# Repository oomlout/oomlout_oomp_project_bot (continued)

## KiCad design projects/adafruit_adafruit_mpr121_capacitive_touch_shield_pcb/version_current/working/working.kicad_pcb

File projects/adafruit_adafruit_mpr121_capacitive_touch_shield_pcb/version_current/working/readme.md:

# OOMP Project  
## Adafruit-MPR121-Capacitive-Touch-Shield-PCB  by adafruit  
  
oomp key: oomp_projects_flat_adafruit_adafruit_mpr121_capacitive_touch_shield_pcb  
(snippet of original readme)  
  
-- Adafruit MPR121 Capacitive Touch Shield PCB  
<a href="http://www.adafruit.com/products/2024"><br/>  
Click here to purchase one from the Adafruit shop</a>  
  
This touch-able add on shield for Arduinos will inspire your next interactive project with 12 capacitive touch sensors. Capacitive touch sensing works by detecting when a person (or animal) has touched one of the sensor electrodes. Capacitive touch sensing used for stuff like touch-reactive tablets and phones, as well as control panels for appliances, which is where you may have used it before. This shield allows you to create electronics that can react to human touch, with up to 12 individual sensors.  
  
The shield has 12 'figure 8' holes in it that can be gripped onto with alligator clip cables. Attach one side of the clip to the shield and the other side to something electrically conductive (like metal) or full of water (like vegetables or fruit!) Then start up our handy Arduino library to detect when the object is touched. That's pretty much it, very easy! For advanced users, you can also solder to a pad to make a slimmer & more permanent connection. Works great with any Arduino as it only uses the I2C pins (SCL & SDA).  
  
It uses the same chip as our MPR121 12-Key Capacitive Touch Sensor Breakout so you can duplicate the library and code! We have examples for reading touches. Using an Arduino Leonardo and a little bit of creativity you can use it to turn touches into keybo  
  full source readme at [readme_src.md](readme_src.md)  
  
source repo at: [https://github.com/adafruit/Adafruit-MPR121-Capacitive-Touch-Shield-PCB](https://github.com/adafruit/Adafruit-MPR121-Capacitive-Touch-Shield-PCB)  
## Board  

## Schematic  

[schematic pdf](working_schematic.pdf)  
## Images

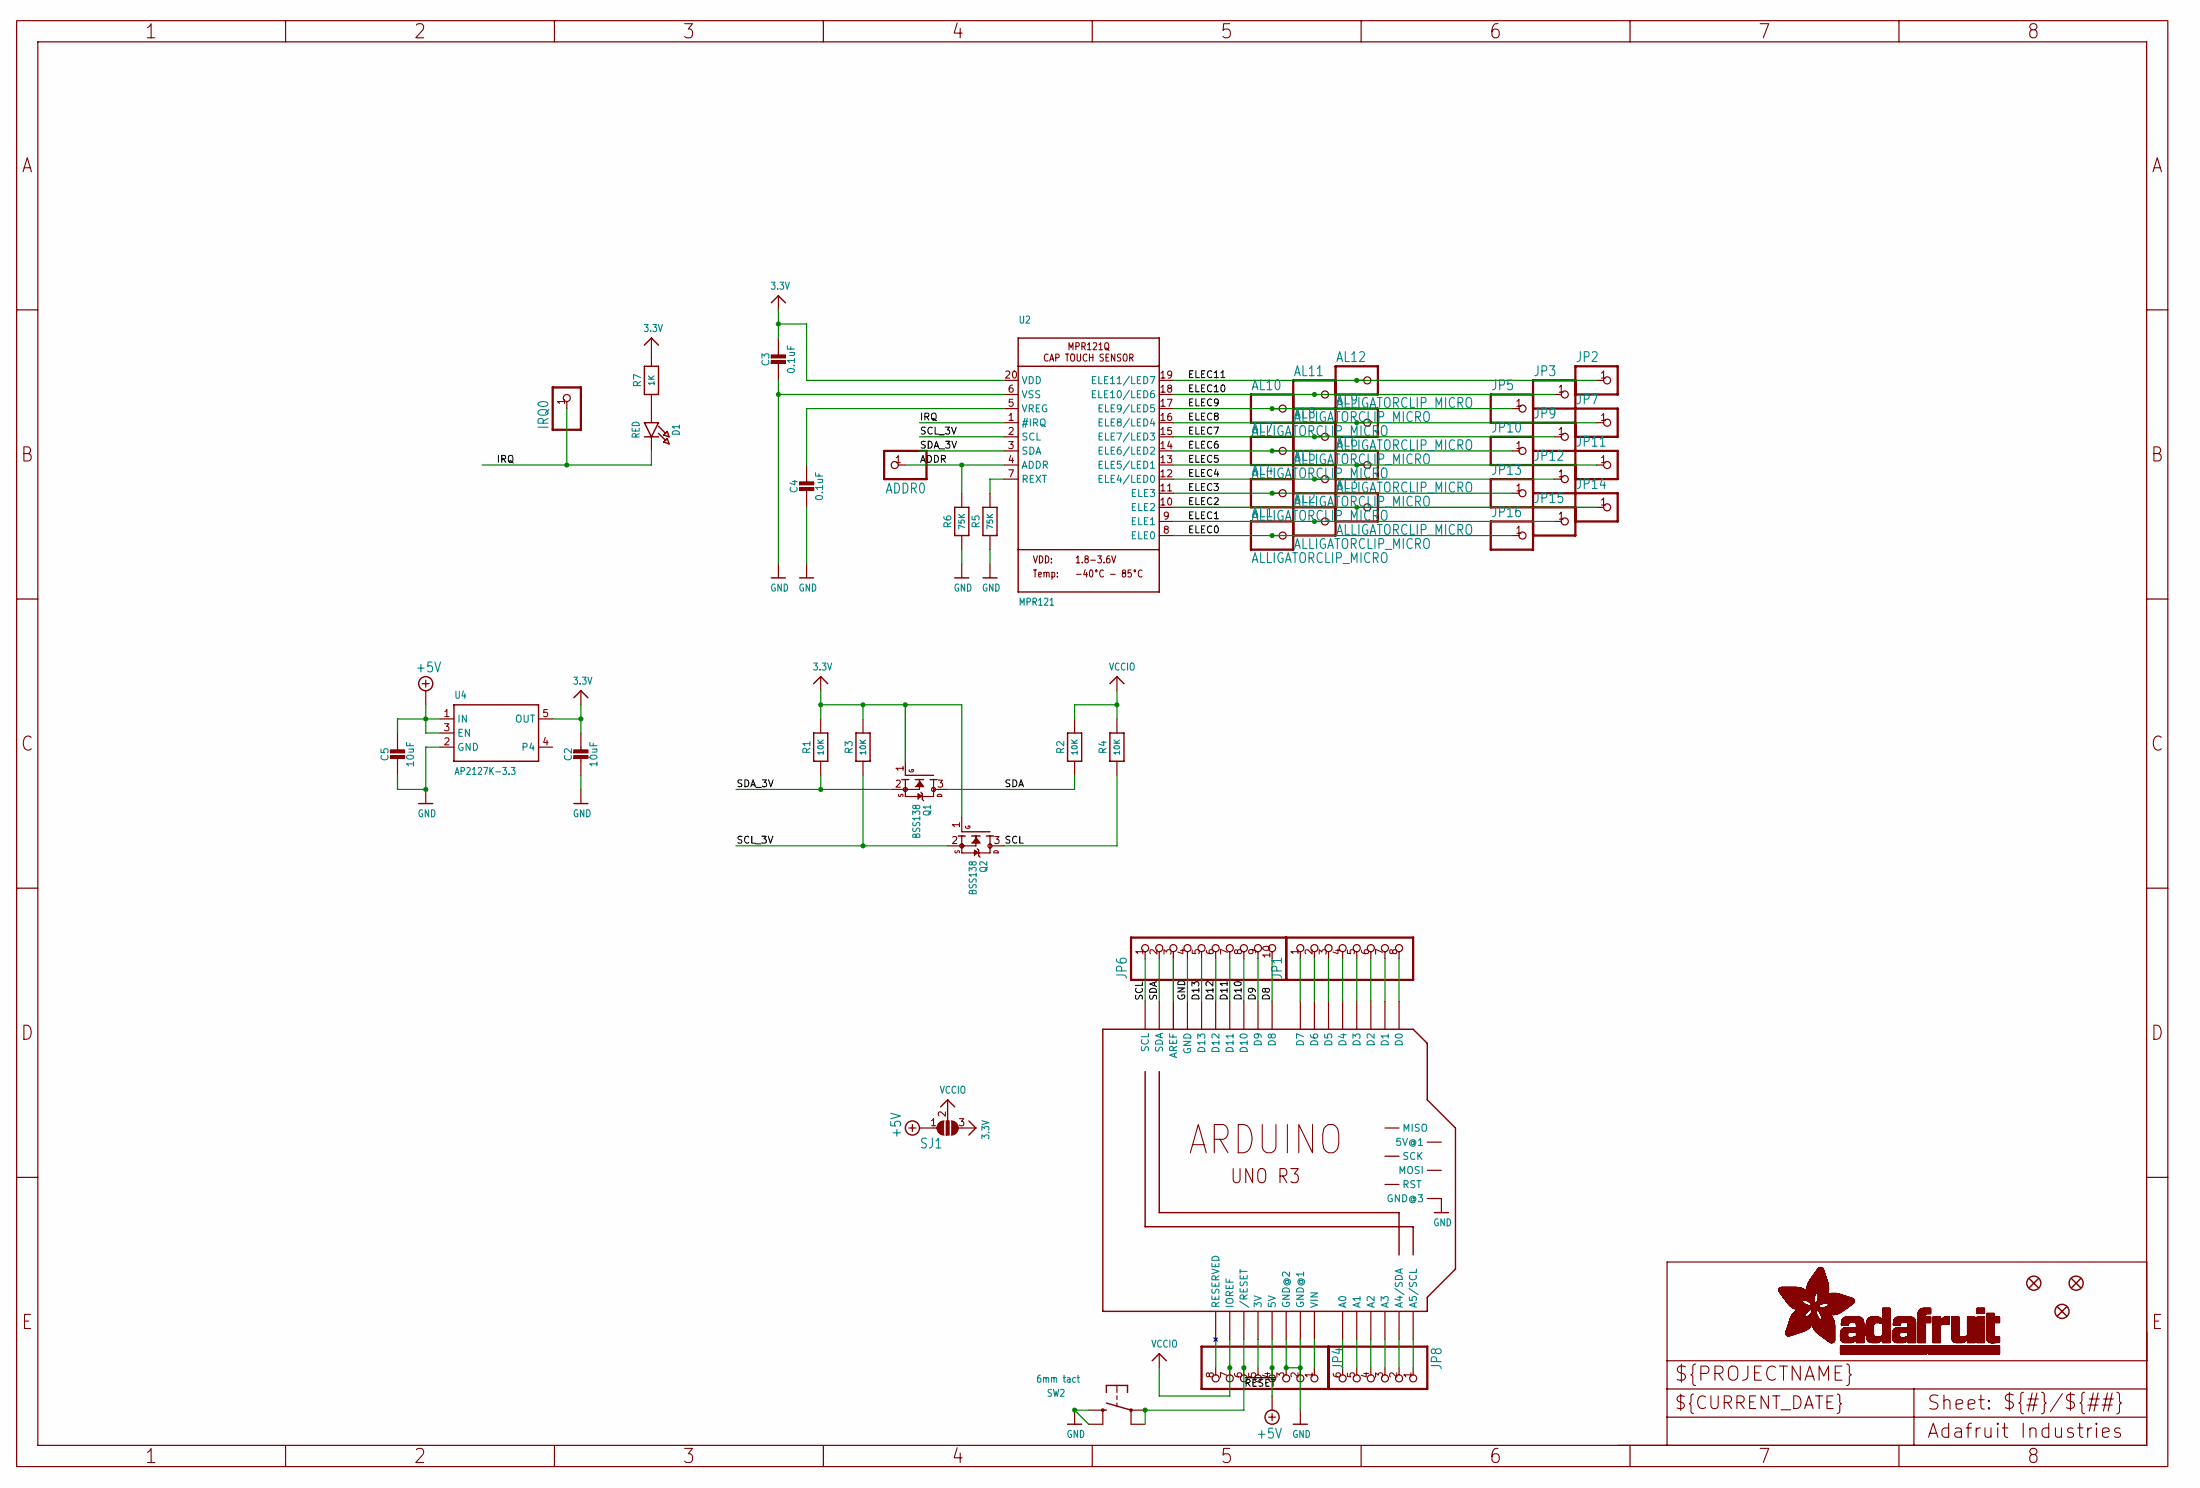
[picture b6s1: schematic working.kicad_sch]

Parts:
ADDR0: HEADER-1X1ROUND; 1X01_ROUND
AL1, AL2, AL3, AL4, AL5, AL6, AL7, AL8, AL9, AL10, AL11, AL12: ALLIGATORCLIP_MICRO; ALLIGATORCLIP
C2, C5: 10uF; 0805-NO
C3, C4: 0.1uF; 0805-NO
D1: RED; CHIPLED_0805_NOOUTLINE
FID1, FID2, FID3: FIDUCIAL_1MM
IRQ0: HEADER-1X1ROUND; 1X01_ROUND
JP1, JP4: PINHD-1X8CLEANBIG; 1X08-CLEANBIG
JP2, JP3, JP5, JP7, JP9, JP10, JP11, JP12, JP13, JP14, JP15, JP16: HEADER-1X1ROUND; 1X01_ROUND
JP6: HEADER-1X1070MIL; 1X10_ROUND70
JP8: PINHD-1X6CB; 1X06-CLEANBIG
Q1, Q2: BSS138; SOT23-WIDE
R1, R2, R3, R4: 10K; 0805-NO
R5, R6: 75K; 0805-NO
R7: 1K; 0805-NO
SJ1: SOLDERJUMPER_2WAY; SOLDERJUMPER_2WAY_OPEN_NOPASTE
SW2: 6mm tact; 6MMX6MM_TACTILE_SMT
U2: MPR121; QFN20_3MM_NOTHERMAL
U4: AP2127K-3.3; SOT23-5
U$41: ARDUINO_R3_ICSP_NODIM; ARDUINOR3_ICSP_NODIM

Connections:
3.3V: C2.1, C3.1, Q1.1 (G), Q2.1 (G), R1.2, R3.2, R7.2, SJ1.3, U2.20 (VDD), U4.5 (OUT)
+3V: JP4.5, U$41.3V
+5V: C5.1, JP4.4, SJ1.1, U4.1 (IN), U4.3 (EN), U$41.5V
A0: JP8.6, U$41.A0
A1: JP8.5, U$41.A1
A2: JP8.4, U$41.A2
A3: JP8.3, U$41.A3
A4: JP8.2, U$41.A4 (A4/SDA)
A5: JP8.1, U$41.A5 (A5/SCL)
ADDR: ADDR0.1, R6.2, U2.4 (ADDR)
AREF: JP6.3, U$41.AREF
D0: JP1.8, U$41.D0
D1: JP1.7, U$41.D1
D2: JP1.6, U$41.D2
D3: JP1.5, U$41.D3
D4: JP1.4, U$41.D4
D5: JP1.3, U$41.D5
D6: JP1.2, U$41.D6
D7: JP1.1, U$41.D7
D8: JP6.10, U$41.D8
D9: JP6.9, U$41.D9
D10: JP6.8, U$41.D10
D11: JP6.7, U$41.D11
D12: JP6.6, U$41.D12
D13: JP6.5, U$41.D13
ELEC0: AL1.P$1, AL1.P$2, JP16.1, U2.8 (ELE0)
ELEC1: AL2.P$1, AL2.P$2, JP15.1, U2.9 (ELE1)
ELEC2: AL3.P$1, AL3.P$2, JP14.1, U2.10 (ELE2)
ELEC3: AL4.P$1, AL4.P$2, JP13.1, U2.11 (ELE3)
ELEC4: AL5.P$1, AL5.P$2, JP12.1, U2.12 (ELE4/LED0)
ELEC5: AL6.P$1, AL6.P$2, JP11.1, U2.13 (ELE5/LED1)
ELEC6: AL7.P$1, AL7.P$2, JP10.1, U2.14 (ELE6/LED2)
ELEC7: AL8.P$1, AL8.P$2, JP9.1, U2.15 (ELE7/LED3)
ELEC8: AL9.P$1, AL9.P$2, JP7.1, U2.16 (ELE8/LED4)
ELEC9: AL10.P$1, AL10.P$2, JP5.1, U2.17 (ELE9/LED5)
ELEC10: AL11.P$1, AL11.P$2, JP3.1, U2.18 (ELE10/LED6)
ELEC11: AL12.P$1, AL12.P$2, JP2.1, U2.19 (ELE11/LED7)
GND: C2.2, C3.2, C4.2, C5.2, JP4.2, JP4.3, JP6.4, R5.1, R6.1, SW2.B (S), SW2.B' (S1), U2.6 (VSS), U4.2 (GND), U$41.GND, U$41.GND@1 (GND@2), U$41.GND@2 (GND@3), U$41.GND@3 (GND@1)
IRQ: D1.C, IRQ0.1, U2.1 (#IRQ)
unnamed: C4.1, U2.5 (VREG)
unnamed: R5.2, U2.7 (REXT)
unnamed: D1.A, R7.1
NC: JP4.8, U$41.RESERVED
SCL: JP6.1, Q2.3 (D), R4.1, U$41.SCL
SCL_3V: Q2.2 (S), R3.1, U2.2 (SCL)
SDA: JP6.2, Q1.3 (D), R2.1, U$41.SDA
SDA_3V: Q1.2 (S), R1.1, U2.3 (SDA)
VCCIO: JP4.7, R2.2, R4.2, SJ1.2, U$41.IOREF
VIN: JP4.1, U$41.VIN
~RESET: JP4.6, SW2.A, SW2.A' (P1), U$41.RESET (/RESET)

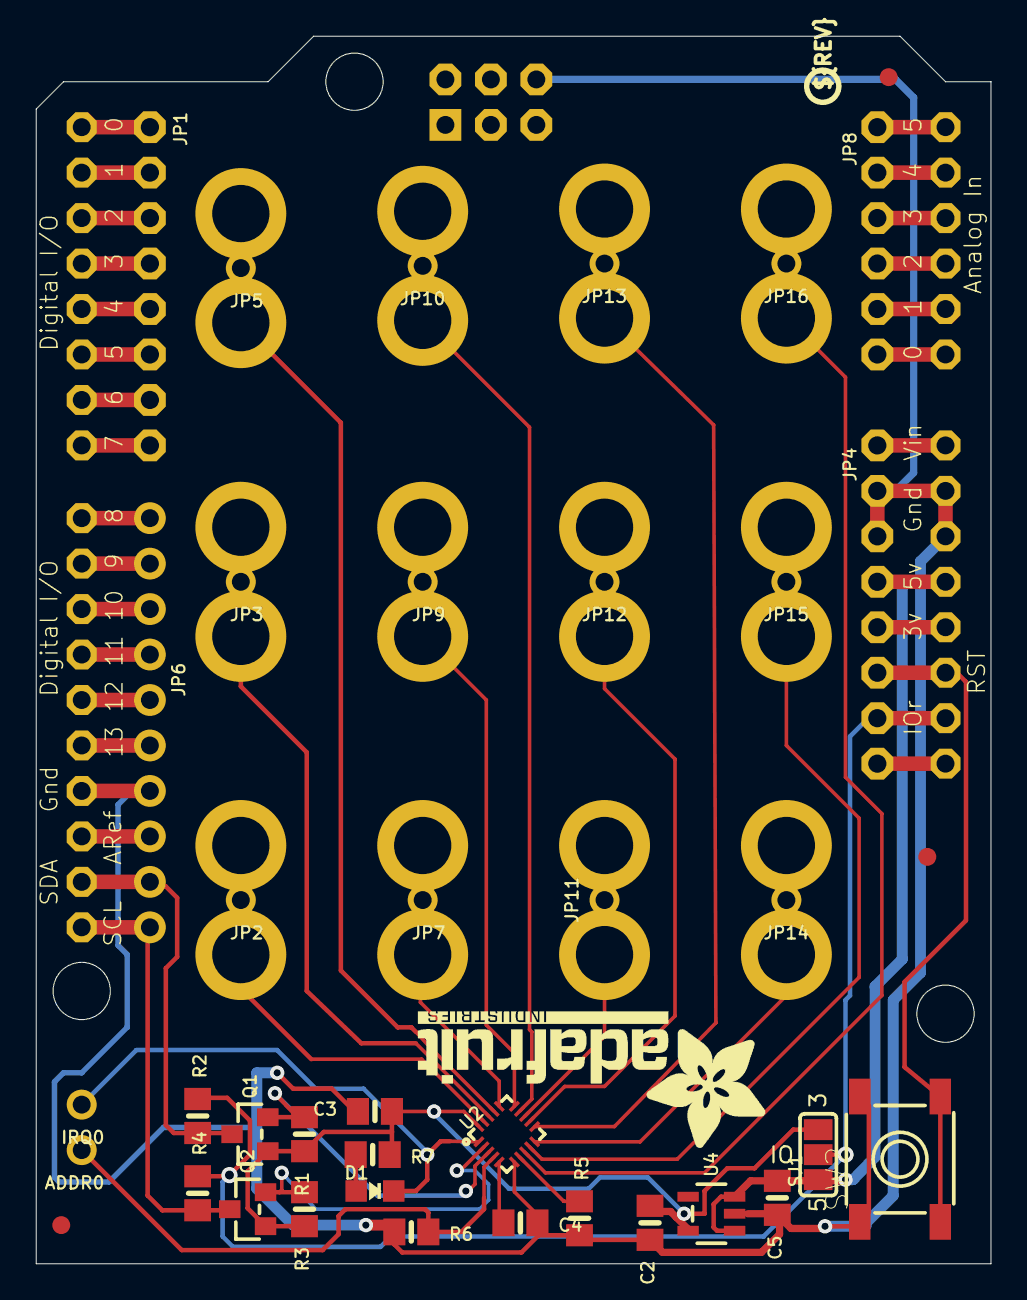
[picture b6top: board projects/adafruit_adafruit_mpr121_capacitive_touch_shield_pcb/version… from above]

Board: 2 copper layers, 53.3 x 68.6 mm, 75 parts (0 on the bottom side), 50 nets.

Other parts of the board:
@HOLE0, @HOLE1, @HOLE2: (no value)
PLABEL0: PLABEL0
PLABEL1: PLABEL1
PLABEL2: PLABEL2
PLABEL3: PLABEL3
PLABEL4: PLABEL4
PLABEL5: PLABEL5
PLABEL6: PLABEL6
PLABEL7: PLABEL7
PLABEL8: PLABEL8
PLABEL9: PLABEL9
PLABEL10: PLABEL10
PLABEL11: PLABEL11
PLABEL12: PLABEL12
PLABEL13: PLABEL13
PLABEL14: PLABEL14
PLABEL15: PLABEL15
PLABEL16: PLABEL16
PLABEL17: PLABEL17
U$8: PCBFEAT-REV-040
U$9: ADAFRUIT_TEXT_20MM

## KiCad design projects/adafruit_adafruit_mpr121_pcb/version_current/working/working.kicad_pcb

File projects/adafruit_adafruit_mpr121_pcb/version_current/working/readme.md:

# OOMP Project  
## Adafruit-MPR121-PCB  by adafruit  
  
oomp key: oomp_projects_flat_adafruit_adafruit_mpr121_pcb  
(snippet of original readme)  
  
-- Adafruit MPR121 capacitive touch breakout PCB  
<a href="http://www.adafruit.com/products/1982"><br/>  
Click here to purchase one from the Adafruit shop</a>  
<a href="http://www.adafruit.com/products/4830"><br/>  
Click here to purchase one from the Adafruit shop</a>  
  
Add lots of touch sensors to your next microcontroller project with this easy-to-use 12-channel capacitive touch sensor breakout board, starring the MPR121. This chip can handle up to 12 individual touch pads.  
  
The MPR121 has support for only I2C, which can be implemented with nearly any microcontroller. You can select one of 4 addresses with the ADDR pin (or two on the Gator version), for a total of 48 (24 on the Gator version) capacitive touch pads on one I2C 2-wire bus. Using this chip is a lot easier than doing the capacitive sensing with analog inputs: it handles all the filtering for you and can be configured for more/less sensitivity.  
  
This sensor comes as a tiny hard-to-solder chip so we put it onto a breakout board for you. Since it's a 3V-only chip, we added a 3V regulator and I2C level shifting so its safe to use with any 3V or 5V microcontroller/processor like Arduino. We even added an LED onto the IRQ line so it will blink when touches are detected, making debugging by sight a bit easier on you. Comes with a fully assembled board, and a stick of 0.1" header so you can plug it into a breadboard. For conta  
  full source readme at [readme_src.md](readme_src.md)  
  
source repo at: [https://github.com/adafruit/Adafruit-MPR121-PCB](https://github.com/adafruit/Adafruit-MPR121-PCB)  
## Board  

## Schematic  

[schematic pdf](working_schematic.pdf)  
## Images

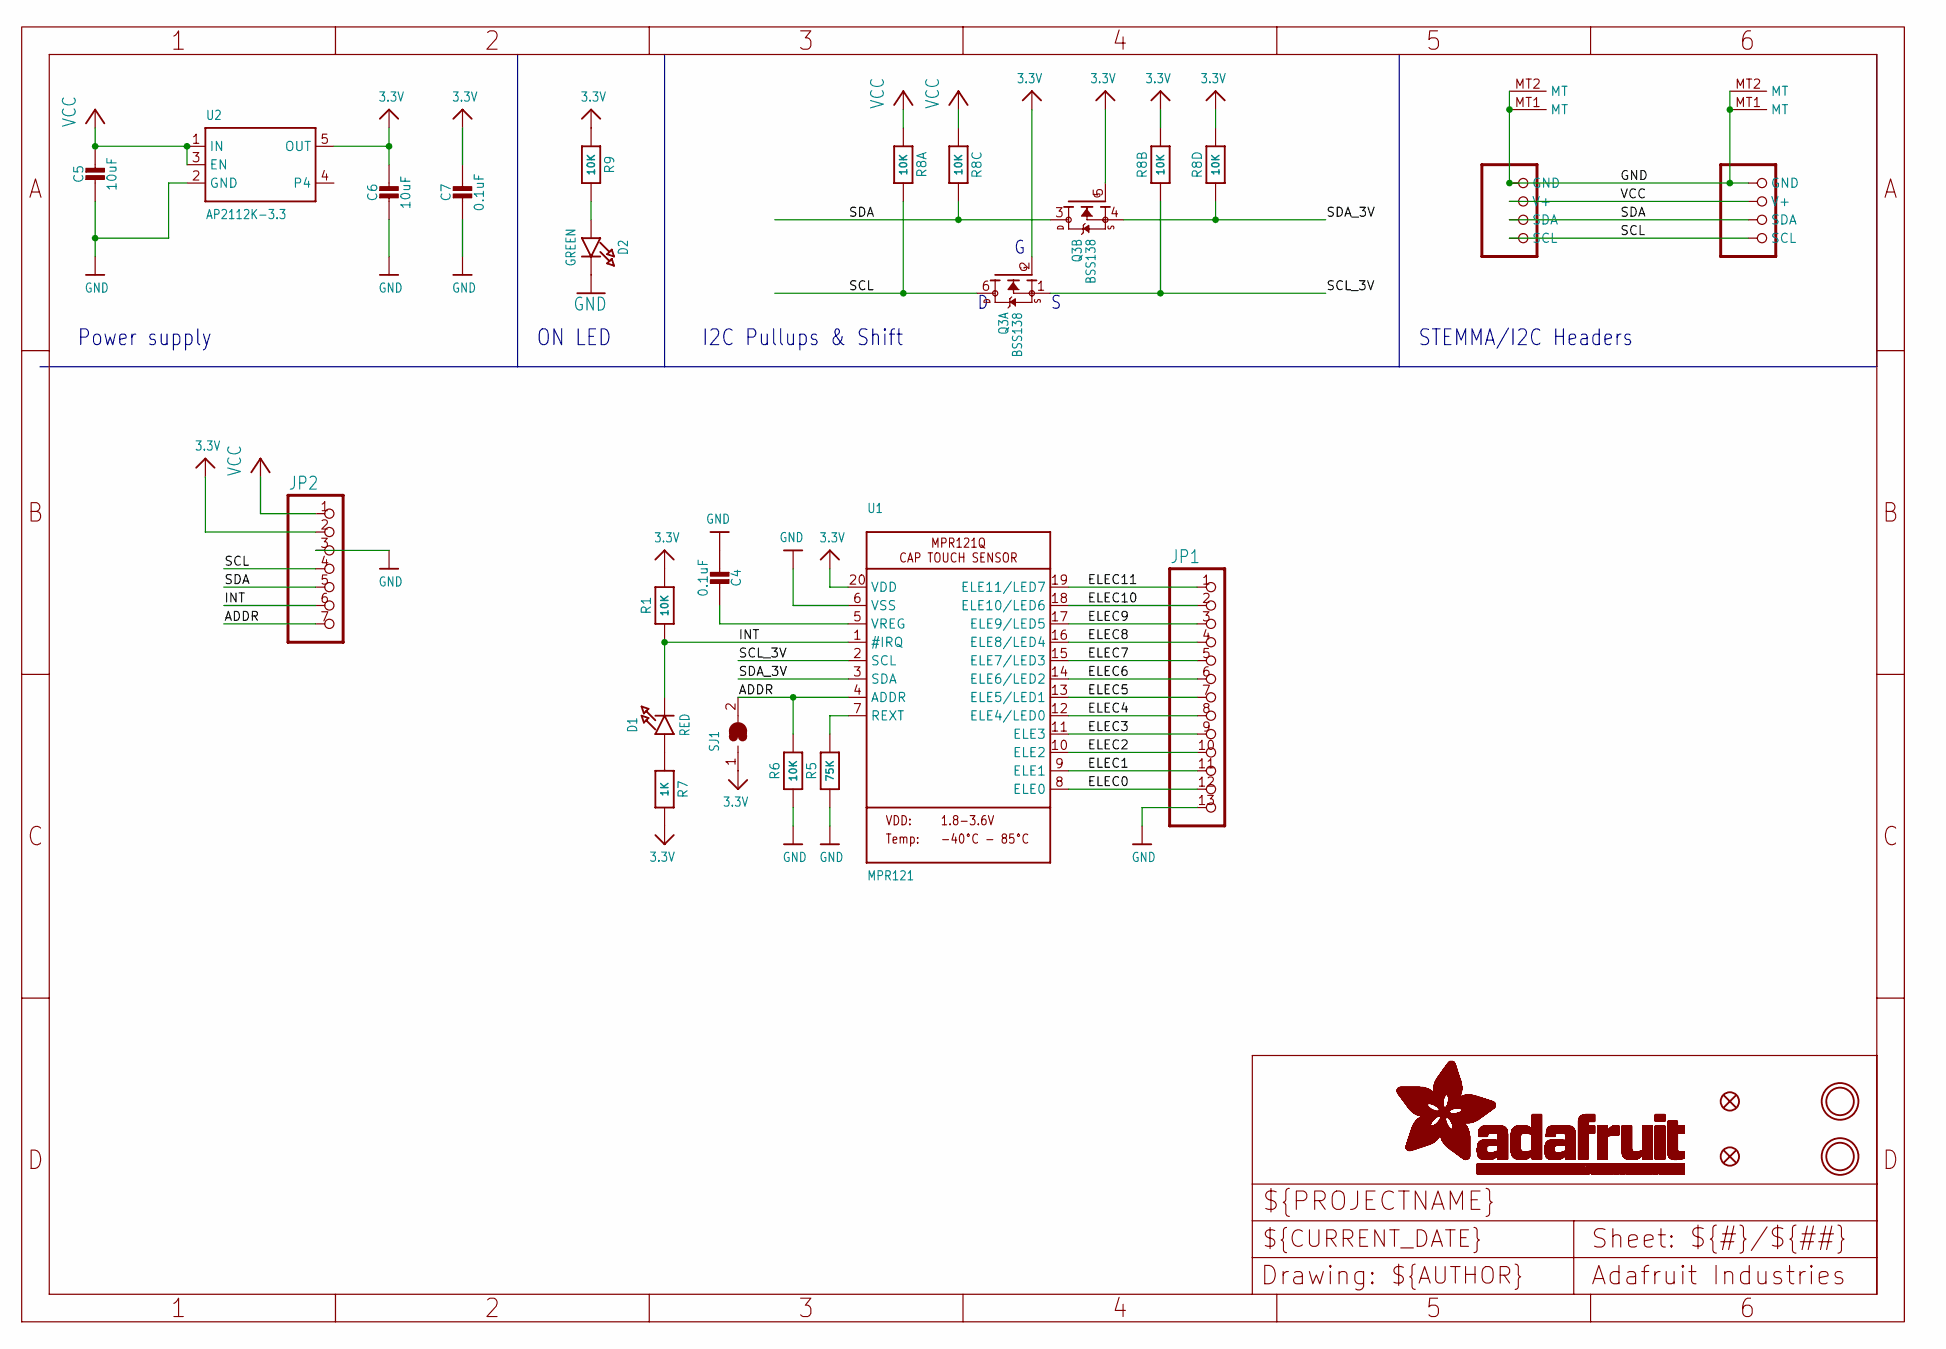
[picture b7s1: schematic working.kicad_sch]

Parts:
C4, C7: 0.1uF; 0603-NO
C5, C6: 10uF; 0805-NO
CONN3, CONN4: STEMMA_I2C_QT; JST_SH4
D1: RED; CHIPLED_0603_NOOUTLINE
D2: GREEN; CHIPLED_0603_NOOUTLINE
FID3, FID4: FIDUCIAL_1MM
JP1: HEADER-1X13; 1X13_ROUND_70
JP2: HEADER-1X770MIL; 1X07_ROUND_70
Q3: BSS138; SOT363
R1, R6, R9: 10K; 0603-NO
R5: 75K; 0603-NO
R7: 1K; 0603-NO
R8: 10K; RESPACK_4X0603
SJ1: SOLDERJUMPER; SOLDERJUMPER_ARROW_NOPASTE
U1: MPR121; QFN20_3MM_NOTHERMAL
U2: AP2112K-3.3; SOT23-5
U$34, U$35: MOUNTINGHOLE2.5; MOUNTINGHOLE_2.5_PLATED

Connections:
3.3V: C6.1, C7.1, JP2.2, Q3.2 (G), Q3.5 (G), R1.2, R7.2, R8.2 (1), R8.4 (1), R9.1, SJ1.1, U1.20 (VDD), U2.5 (OUT)
ADDR: JP2.7, R6.2, SJ1.2, U1.4 (ADDR)
ELEC0: JP1.12, U1.8 (ELE0)
ELEC1: JP1.11, U1.9 (ELE1)
ELEC2: JP1.10, U1.10 (ELE2)
ELEC3: JP1.9, U1.11 (ELE3)
ELEC4: JP1.8, U1.12 (ELE4/LED0)
ELEC5: JP1.7, U1.13 (ELE5/LED1)
ELEC6: JP1.6, U1.14 (ELE6/LED2)
ELEC7: JP1.5, U1.15 (ELE7/LED3)
ELEC8: JP1.4, U1.16 (ELE8/LED4)
ELEC9: JP1.3, U1.17 (ELE9/LED5)
ELEC10: JP1.2, U1.18 (ELE10/LED6)
ELEC11: JP1.1, U1.19 (ELE11/LED7)
GND: C4.2, C5.2, C6.2, C7.2, CONN3.1 (GND), CONN3.MT1 (MT), CONN3.MT2 (MT), CONN4.1 (GND), CONN4.MT1 (MT), CONN4.MT2 (MT), D2.C, JP1.13, JP2.3, R5.1, R6.1, U1.6 (VSS), U2.2 (GND)
INT: D1.C, JP2.6, R1.1, U1.1 (#IRQ)
unnamed: D1.A, R7.1
unnamed: C4.1, U1.5 (VREG)
unnamed: R5.2, U1.7 (REXT)
unnamed: D2.A, R9.2
SCL: CONN3.4 (SCL), CONN4.4 (SCL), JP2.4, Q3.6 (D), R8.8 (2)
SCL_3V: Q3.1 (S), R8.7 (2), U1.2 (SCL)
SDA: CONN3.3 (SDA), CONN4.3 (SDA), JP2.5, Q3.3 (D), R8.6 (2)
SDA_3V: Q3.4 (S), R8.5 (2), U1.3 (SDA)
VCC: C5.1, CONN3.2 (V+), CONN4.2 (V+), JP2.1, R8.1, R8.3 (1), U2.1 (IN), U2.3 (EN)

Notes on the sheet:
ON LED
Power supply
STEMMA/I2C Headers
I2C Pullups & Shift

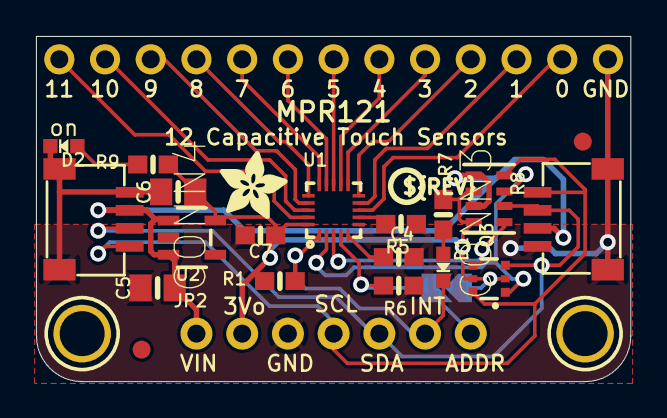
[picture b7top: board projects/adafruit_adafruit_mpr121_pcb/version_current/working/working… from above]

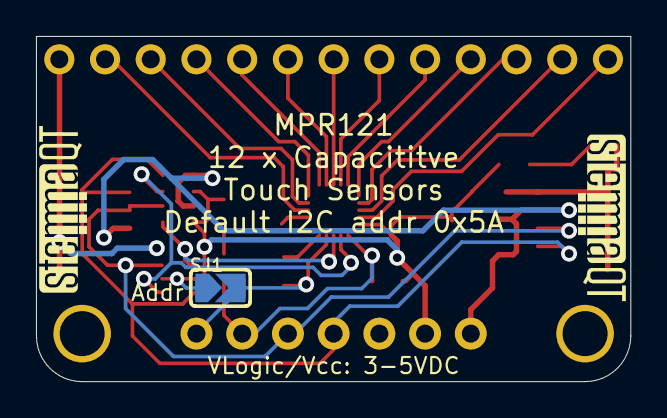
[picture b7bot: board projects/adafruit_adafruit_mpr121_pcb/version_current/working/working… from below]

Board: 2 copper layers, 33.0 x 19.2 mm, 28 parts (3 on the bottom side), 25 nets.

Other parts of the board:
U$9: PCBFEAT-REV-040
U$37: ADAFRUIT_3.5MM
U$39, U$40: STEMMAQT
